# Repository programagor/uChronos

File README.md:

# uChronos
OSHW wristwatch which shows time in BCD

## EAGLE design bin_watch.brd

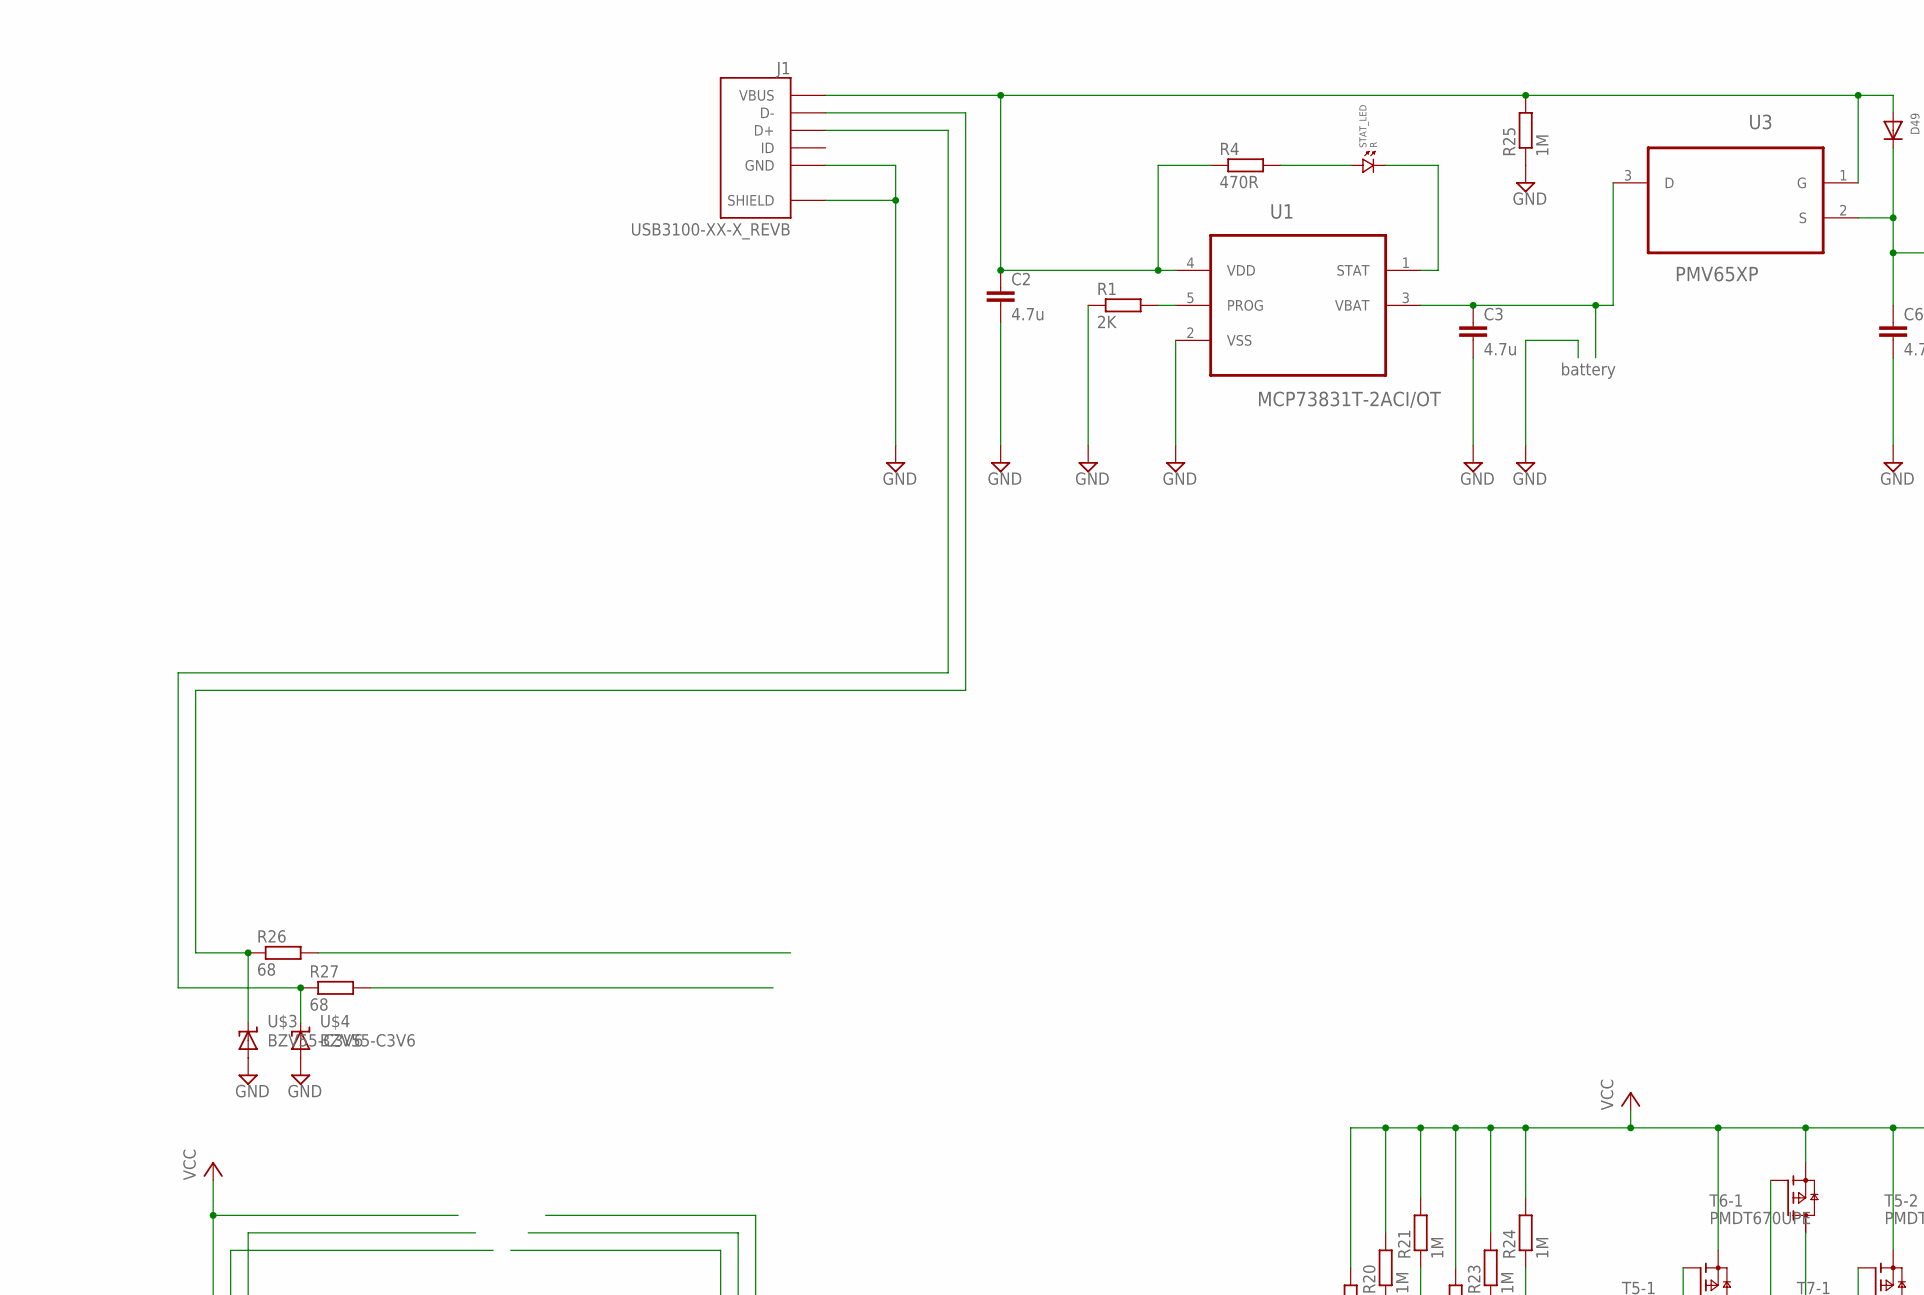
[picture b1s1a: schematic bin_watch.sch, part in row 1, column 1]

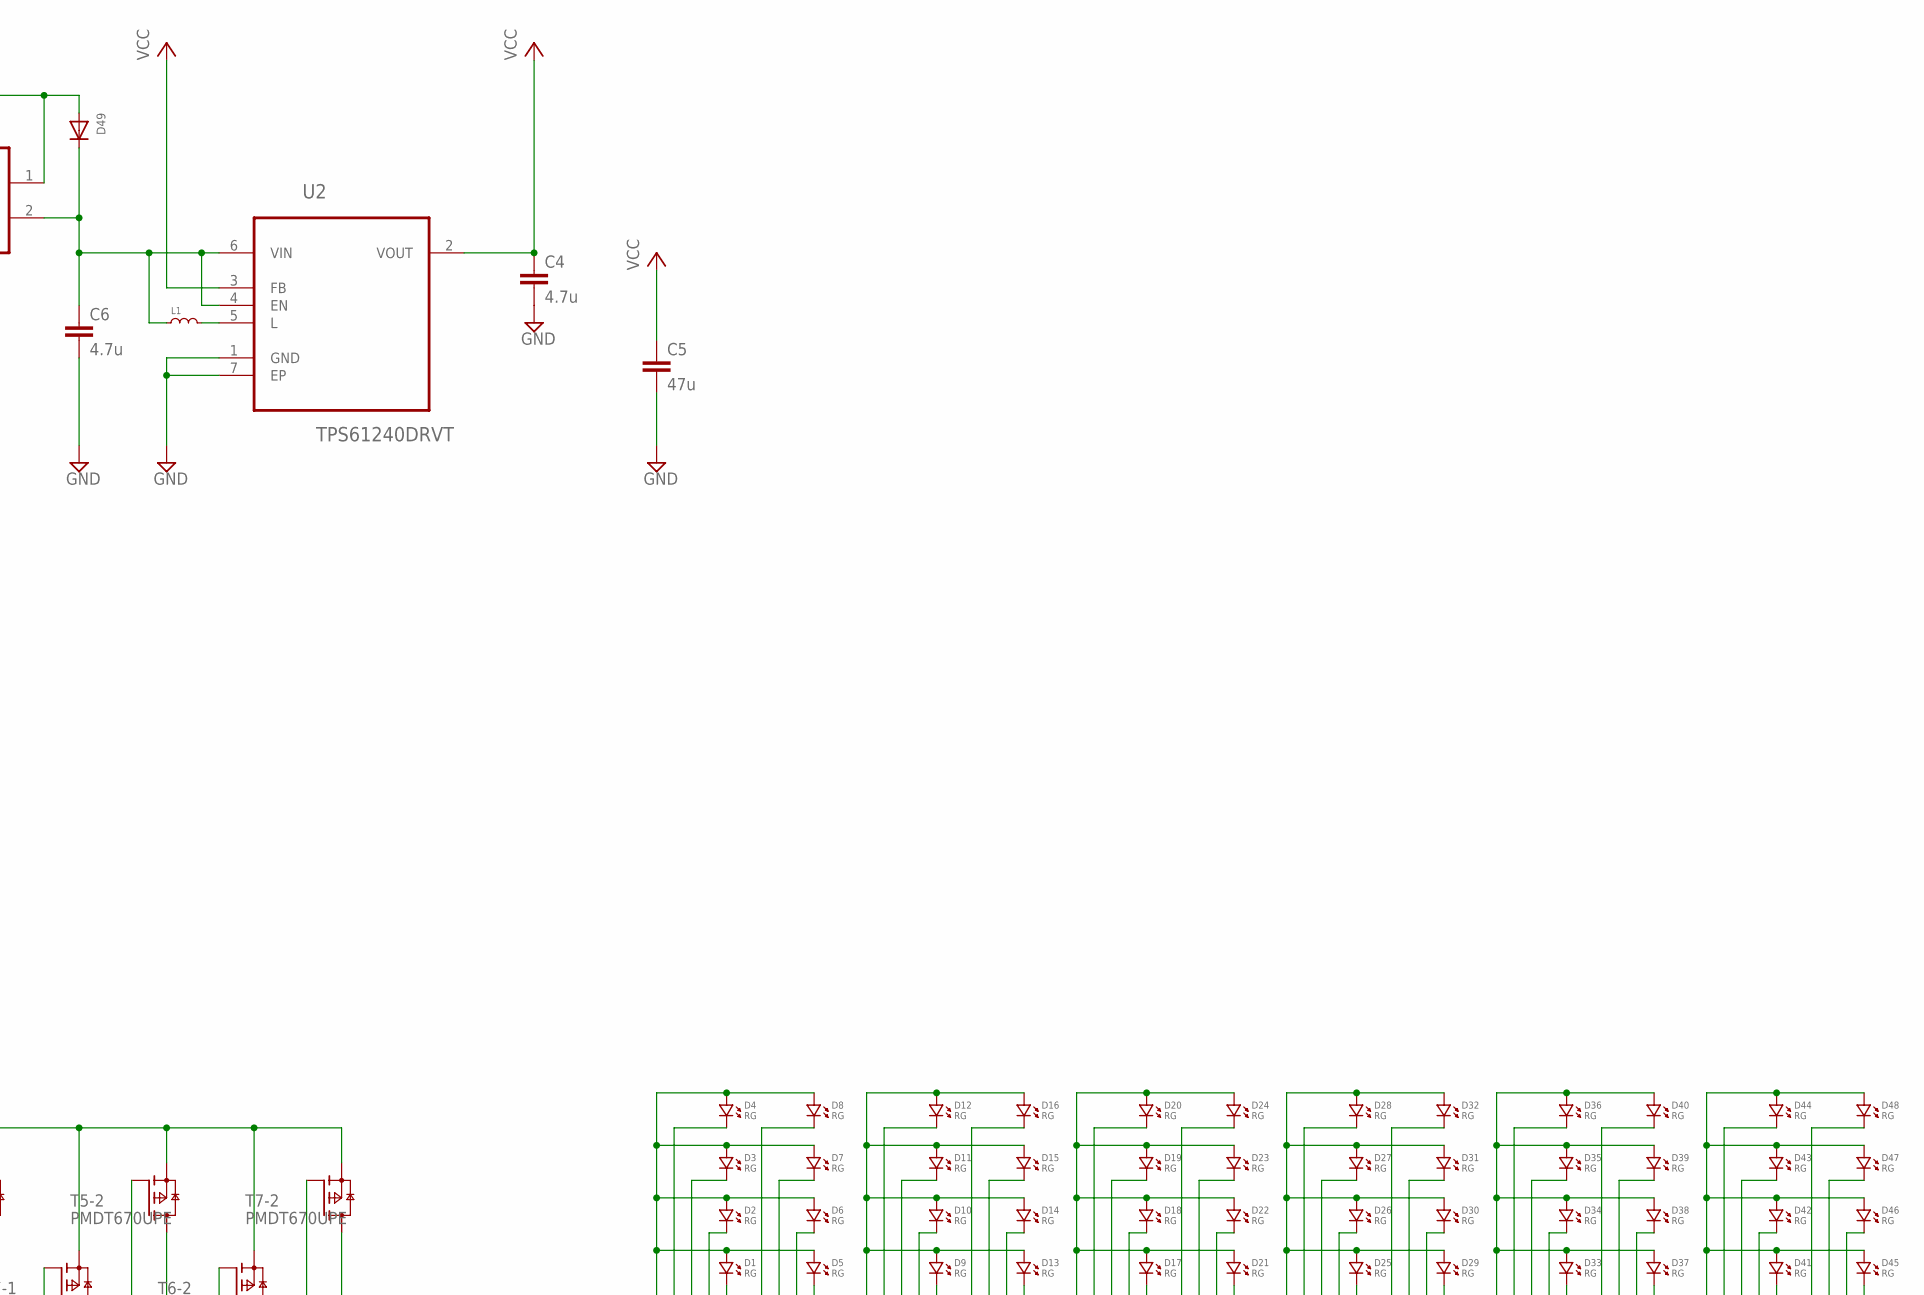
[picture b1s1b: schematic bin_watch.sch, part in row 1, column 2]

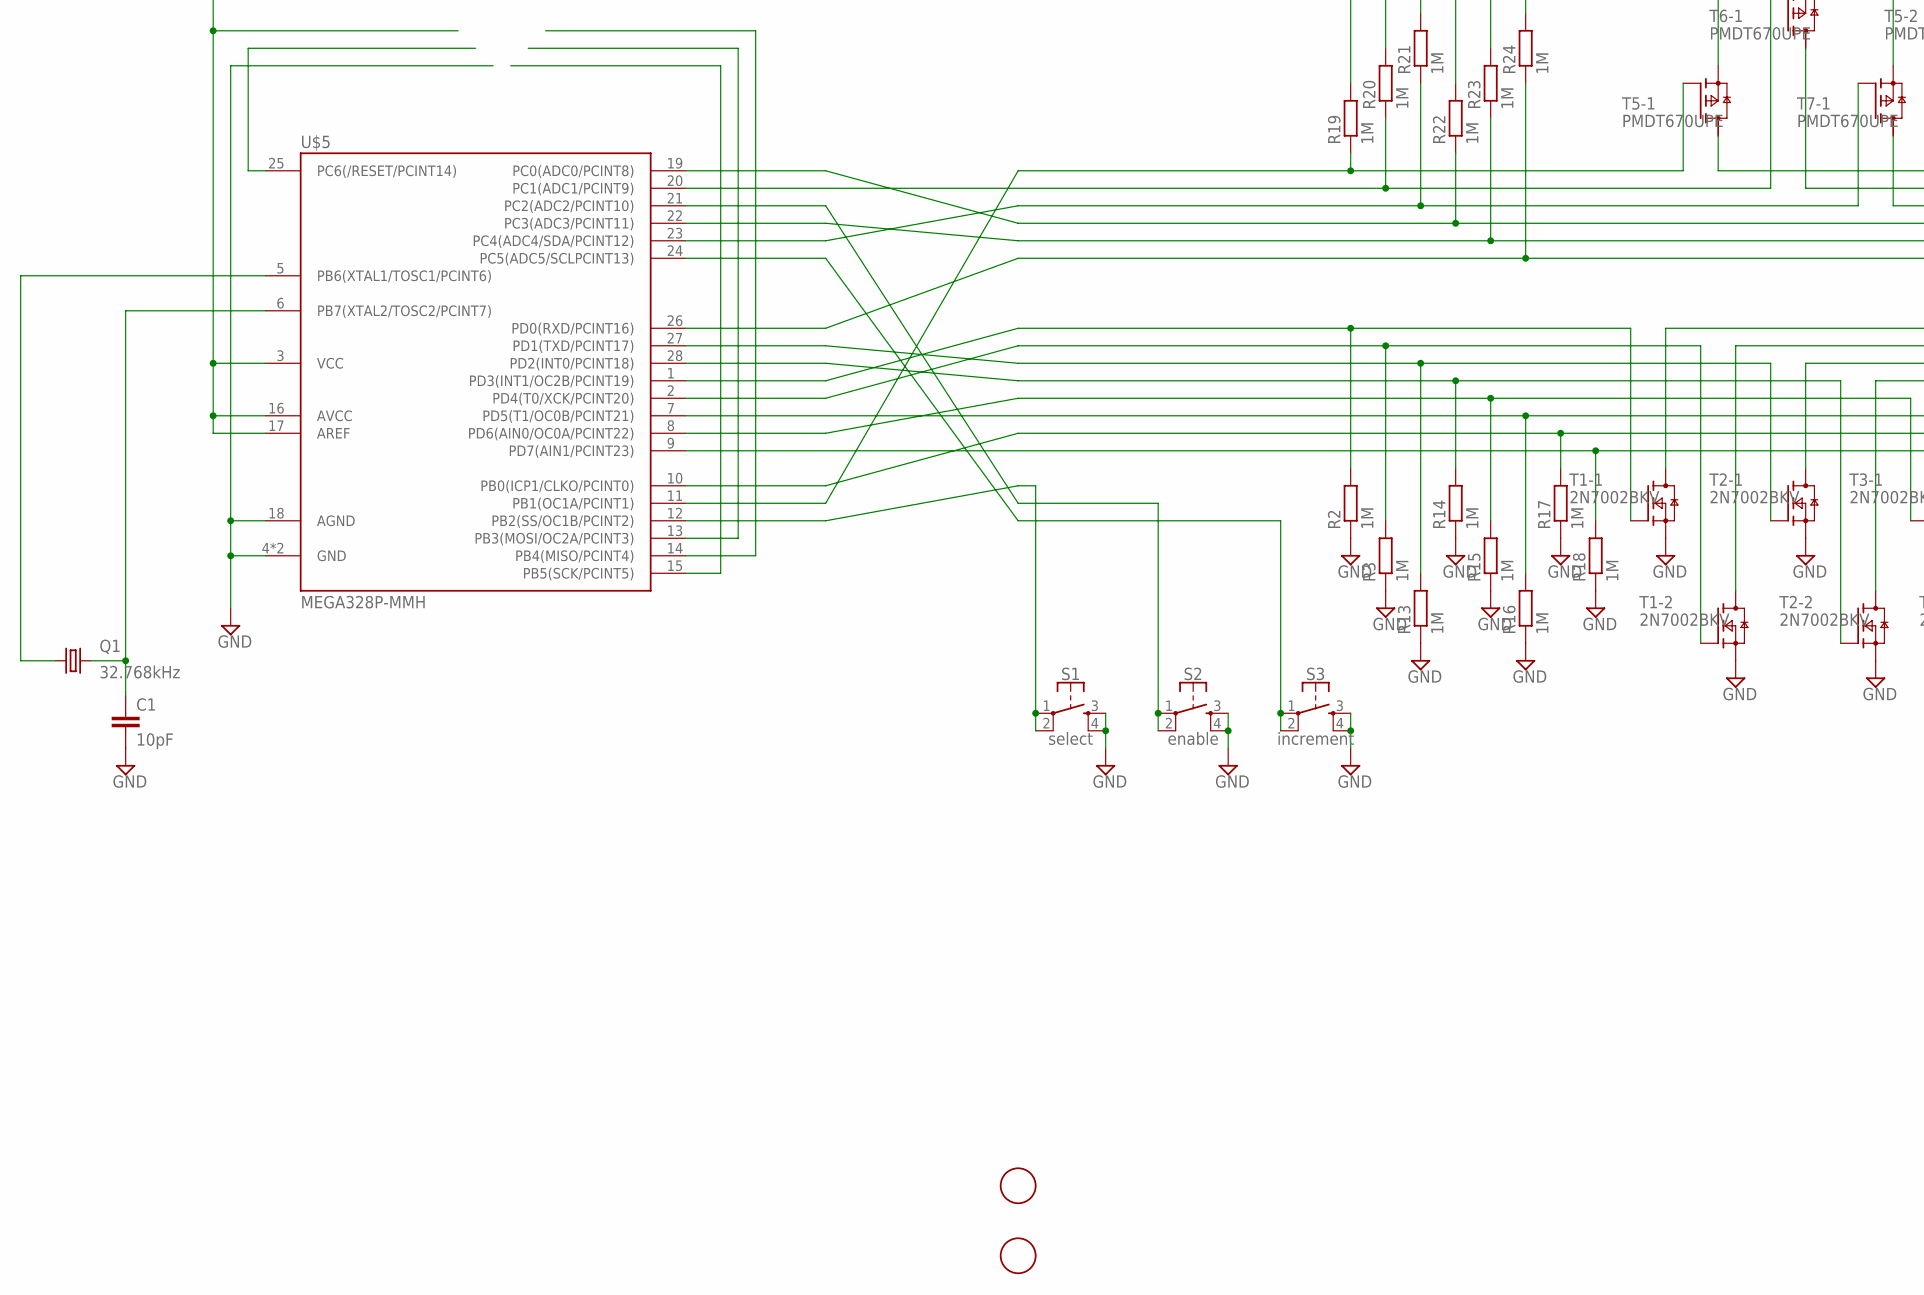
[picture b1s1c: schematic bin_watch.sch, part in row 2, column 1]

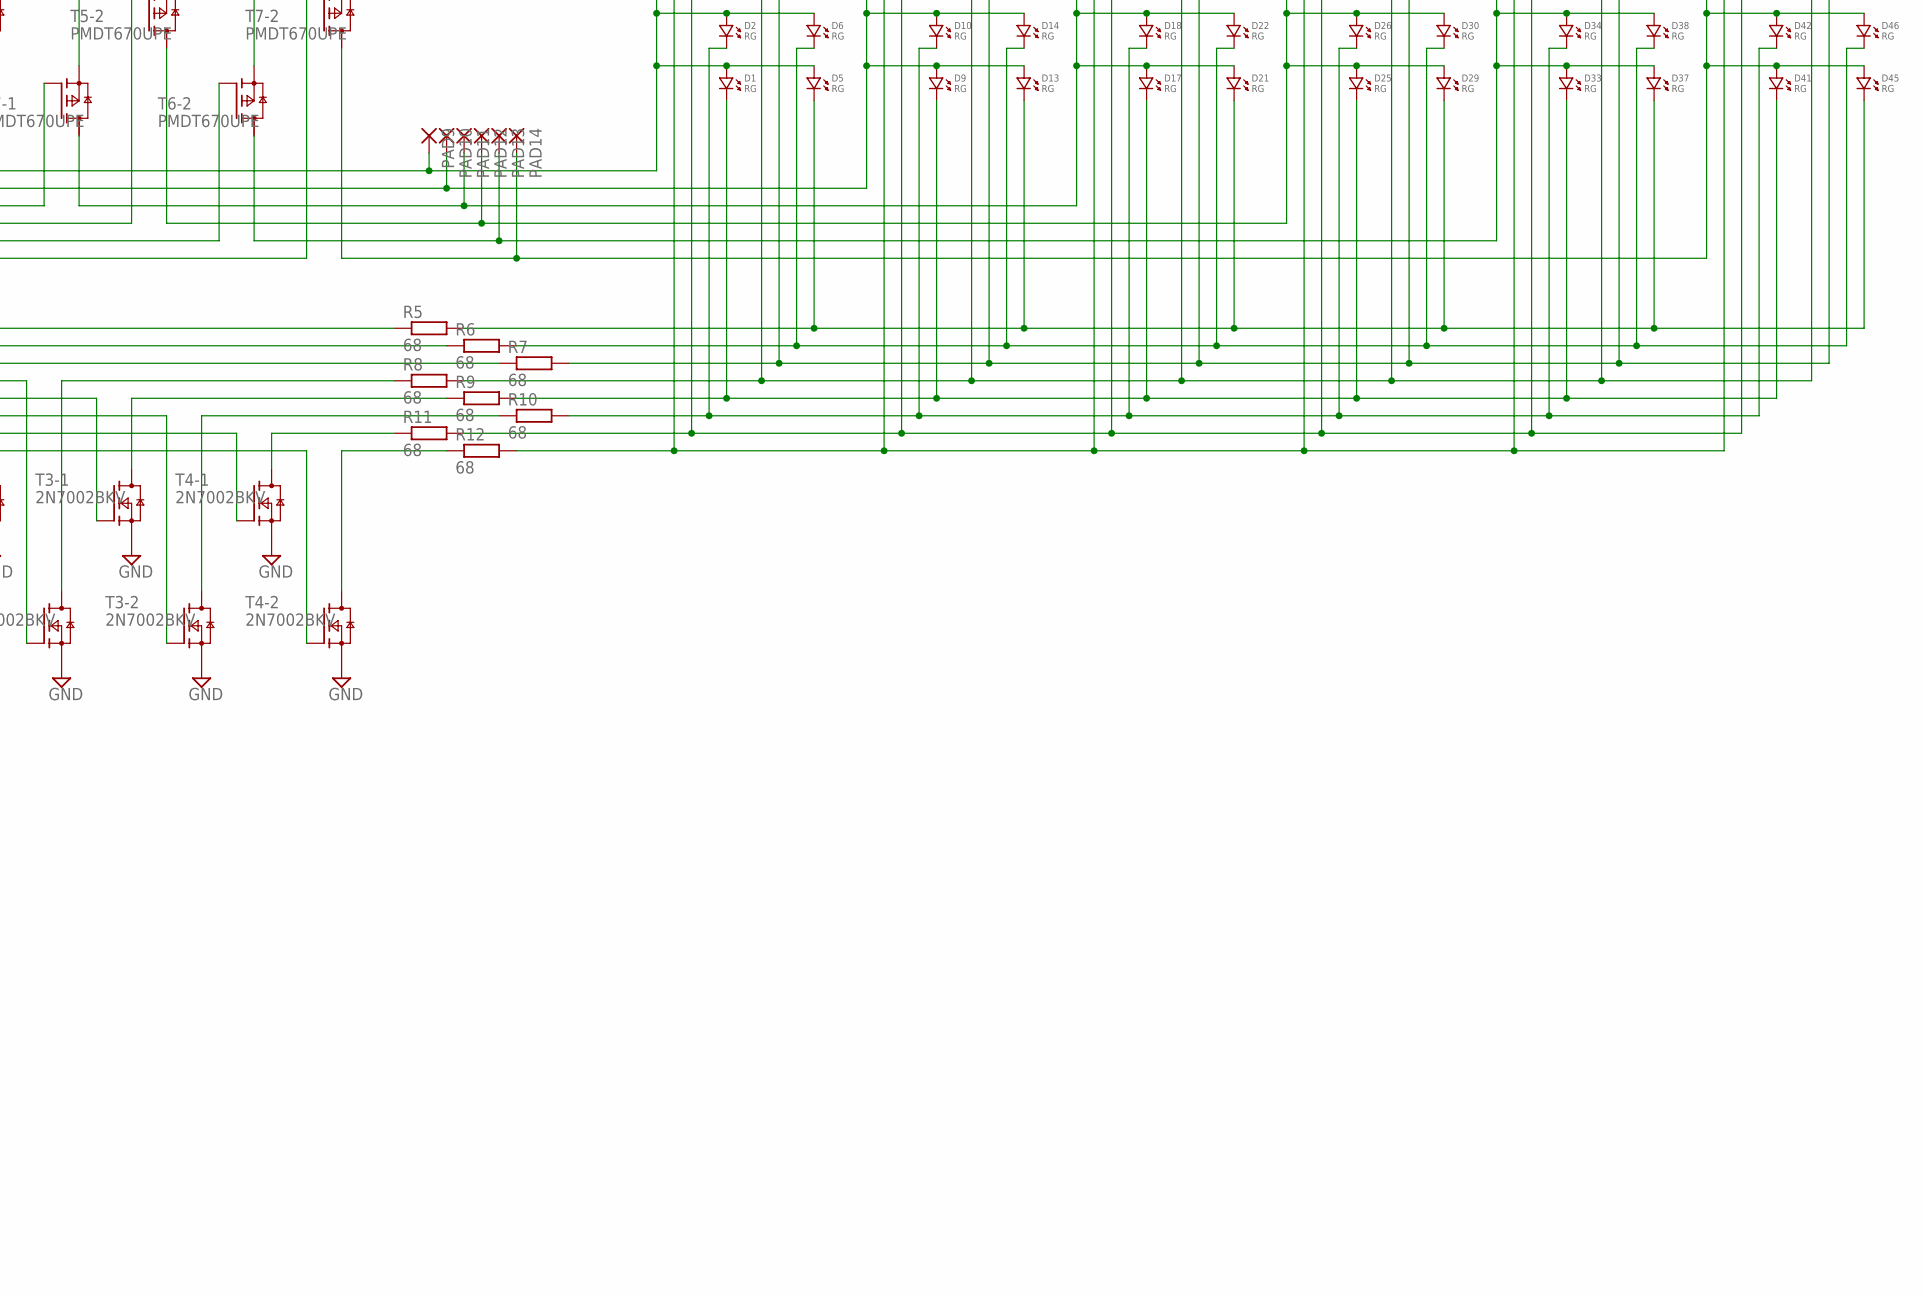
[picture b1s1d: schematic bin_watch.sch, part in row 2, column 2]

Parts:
C1: 10pF; C0603
C2, C3, C4, C6: 4.7u; C0603
C5: 47u; C0603
D1, D2, D3, D4, D5, D6, D7, D8, D9, D10, D11, D12, D13, D14, D15, D16, D17, D18, D19, D20, D21, D22, D23, D24, D25, D26, D27, D28, D29, D30, D31, D32, D33, D34, D35, D36, D37, D38, D39, D40, D41, D42, D43, D44, D45, D46, D47, D48: RG; 0603.LED
D49: DIODESOD-523; SOD-523
J1: USB3100-XX-X_REVB; GCT_USB3100-XX-X_REVB
L1: RF-INDUCTOR.0805; 0805
PAD9, PAD10, PAD11, PAD12, PAD13, PAD14: SMD2; SMD1,27-2,54
Q1: 32.768kHz; 3.2X1.5
R1: 2K; R0603
R2, R3, R13, R14, R15, R16, R17, R18, R19, R20, R21, R22, R23, R24, R25: 1M; R0603
R4: 470R; R0603
R5, R6, R7, R8, R9, R10, R11, R12, R26, R27: 68; R0603
S1: select; TACTILE_SWITCH_SMD_5.2MM
S2: enable; TACTILE_SWITCH_SMD_5.2MM
S3: increment; TACTILE_SWITCH_SMD_5.2MM
STAT_LED: R; 0603.LED
T1, T2, T3, T4: 2N7002BKV; SOT666
T5, T6, T7: PMDT670UPE; SOT666
U1: MCP73831T-2ACI/OT; SOT95P280X145-5N
U2: TPS61240DRVT; SON65P200X200X80-7N
U3: PMV65XP; SOT95P230X110-3N
U$1, U$2: FIDUCIAL; FIDUCIAL_1MM
U$3, U$4: BZV55-C3V6; SOD-80
U$5: MEGA328P-MMH; VQFN28

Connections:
BLOCK0: D1.P$1 (1), D2.P$1 (1), D3.P$1 (1), D4.P$1 (1), D5.P$1 (1), D6.P$1 (1), D7.P$1 (1), D8.P$1 (1), PAD9.1, T5.6 (D)
BLOCK1: D9.P$1 (1), D10.P$1 (1), D11.P$1 (1), D12.P$1 (1), D13.P$1 (1), D14.P$1 (1), D15.P$1 (1), D16.P$1 (1), PAD10.1, T6.6 (D)
BLOCK2: D17.P$1 (1), D18.P$1 (1), D19.P$1 (1), D20.P$1 (1), D21.P$1 (1), D22.P$1 (1), D23.P$1 (1), D24.P$1 (1), PAD11.1, T7.6 (D)
BLOCK3: D25.P$1 (1), D26.P$1 (1), D27.P$1 (1), D28.P$1 (1), D29.P$1 (1), D30.P$1 (1), D31.P$1 (1), D32.P$1 (1), PAD12.1, T5.3 (D)
BLOCK4: D33.P$1 (1), D34.P$1 (1), D35.P$1 (1), D36.P$1 (1), D37.P$1 (1), D38.P$1 (1), D39.P$1 (1), D40.P$1 (1), PAD13.1, T6.3 (D)
BLOCK5: D41.P$1 (1), D42.P$1 (1), D43.P$1 (1), D44.P$1 (1), D45.P$1 (1), D46.P$1 (1), D47.P$1 (1), D48.P$1 (1), PAD14.1, T7.3 (D)
BTN1: S1.1, S1.2, U$5.12 (PB2(SS/OC1B/PCINT2)); also elsewhere on the board
BTN2: S2.1, S2.2, U$5.21 (PC2(ADC2/PCINT10)); also elsewhere on the board
BTN3: S3.1, S3.2, U$5.24 (PC5(ADC5/SCLPCINT13)); also elsewhere on the board
D_N: J1.2 (D-), R26.1, U$3.C
D_P: J1.3 (D+), R27.1, U$4.C
GND: C1.2, C2.2, C3.2, C4.2, C5.2, C6.2, J1.5 (GND), J1.6 (SHIELD), J1.7 (SHIELD), J1.8 (SHIELD), J1.9 (SHIELD), R1.1, R2.1, R3.1, R13.1, R14.1, R15.1, R16.1, R17.1, R18.1, R25.1, S1.3, S1.4, S2.3, S2.4, S3.3, S3.4, T1.1 (S), T1.4 (S), T2.1 (S), T2.4 (S), T3.1 (S), T3.4 (S), T4.1 (S), T4.4 (S), U1.2 (VSS), U2.1 (GND), U2.7 (EP), U$3.A, U$4.A, U$5.4 (GND), U$5.18 (AGND); also elsewhere on the board
G_BLOCK0: R19.1, T5.2 (G), U$5.11 (PB1(OC1A/PCINT1)); also elsewhere on the board
G_BLOCK1: R20.1, T6.2 (G), U$5.20 (PC1(ADC1/PCINT9)); also elsewhere on the board
G_BLOCK2: R21.1, T7.2 (G), U$5.23 (PC4(ADC4/SDA/PCINT12)); also elsewhere on the board
G_BLOCK3: R22.1, T5.5 (G), U$5.19 (PC0(ADC0/PCINT8)); also elsewhere on the board
G_BLOCK4: R23.1, T6.5 (G), U$5.22 (PC3(ADC3/PCINT11)); also elsewhere on the board
G_BLOCK5: R24.1, T7.5 (G), U$5.26 (PD0(RXD/PCINT16)); also elsewhere on the board
G_LIGHT0: R2.2, T1.2 (G), U$5.1 (PD3(INT1/OC2B/PCINT19)); also elsewhere on the board
G_LIGHT1: R3.2, T1.5 (G), U$5.2 (PD4(T0/XCK/PCINT20)); also elsewhere on the board
G_LIGHT2: R13.2, T2.2 (G), U$5.27 (PD1(TXD/PCINT17)); also elsewhere on the board
G_LIGHT3: R14.2, T2.5 (G), U$5.28 (PD2(INT0/PCINT18)); also elsewhere on the board
G_LIGHT4: R15.2, T3.2 (G), U$5.8 (PD6(AIN0/OC0A/PCINT22)); also elsewhere on the board
G_LIGHT5: R16.2, T3.5 (G), U$5.7 (PD5(T1/OC0B/PCINT21)); also elsewhere on the board
G_LIGHT6: R17.2, T4.2 (G), U$5.10 (PB0(ICP1/CLKO/PCINT0)); also elsewhere on the board
G_LIGHT7: R18.2, T4.5 (G), U$5.9 (PD7(AIN1/PCINT23)); also elsewhere on the board
L: L1.2, U2.5 (L)
LIGHT0: D5.P$2 (2), D13.P$2 (2), D21.P$2 (2), D29.P$2 (2), D37.P$2 (2), D45.P$2 (2), R5.2
LIGHT1: D6.P$2 (2), D14.P$2 (2), D22.P$2 (2), D30.P$2 (2), D38.P$2 (2), D46.P$2 (2), R6.2
LIGHT2: D7.P$2 (2), D15.P$2 (2), D23.P$2 (2), D31.P$2 (2), D39.P$2 (2), D47.P$2 (2), R7.2
LIGHT3: D8.P$2 (2), D16.P$2 (2), D24.P$2 (2), D32.P$2 (2), D40.P$2 (2), D48.P$2 (2), R8.2
LIGHT4: D1.P$2 (2), D9.P$2 (2), D17.P$2 (2), D25.P$2 (2), D33.P$2 (2), D41.P$2 (2), R9.2
LIGHT5: D2.P$2 (2), D10.P$2 (2), D18.P$2 (2), D26.P$2 (2), D34.P$2 (2), D42.P$2 (2), R10.2
LIGHT6: D3.P$2 (2), D11.P$2 (2), D19.P$2 (2), D27.P$2 (2), D35.P$2 (2), D43.P$2 (2), R11.2
LIGHT7: D4.P$2 (2), D12.P$2 (2), D20.P$2 (2), D28.P$2 (2), D36.P$2 (2), D44.P$2 (2), R12.2
PROG: R1.2, U1.5 (PROG)
R_LIGHT0: R5.1, T1.6 (D)
R_LIGHT1: R6.1, T1.3 (D)
R_LIGHT2: R7.1, T2.6 (D)
R_LIGHT3: R8.1, T2.3 (D)
R_LIGHT4: R9.1, T3.6 (D)
R_LIGHT5: R10.1, T3.3 (D)
R_LIGHT6: R11.1, T4.6 (D)
R_LIGHT7: R12.1, T4.3 (D)
STAT: STAT_LED.P$2 (2), U1.1 (STAT)
STAT_R: R4.2, STAT_LED.P$1 (1)
VBATT: C3.1, U1.3 (VBAT), U3.3 (D); also elsewhere on the board
VBUS: C2.1, D49.A, J1.1 (VBUS), R4.1, R25.2, U1.4 (VDD), U3.1 (G)
VCC: C4.1, C5.1, R19.2, R20.2, R21.2, R22.2, R23.2, R24.2, T5.1 (S), T5.4 (S), T6.1 (S), T6.4 (S), T7.1 (S), T7.4 (S), U2.2 (VOUT), U2.3 (FB), U$5.3 (VCC), U$5.16 (AVCC), U$5.17 (AREF); also elsewhere on the board
VIN: C6.1, D49.K (C), L1.1, U2.4 (EN), U2.6 (VIN), U3.2 (S)
XTAL_N: C1.1, Q1.2, U$5.6 (PB7(XTAL2/TOSC2/PCINT7)); also elsewhere on the board
XTAL_P: Q1.1, U$5.5 (PB6(XTAL1/TOSC1/PCINT6)); also elsewhere on the board

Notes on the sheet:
battery

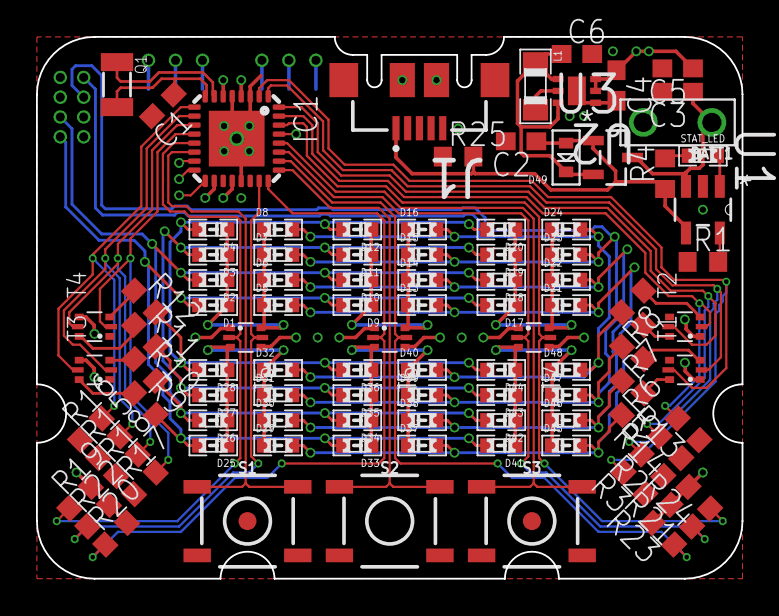
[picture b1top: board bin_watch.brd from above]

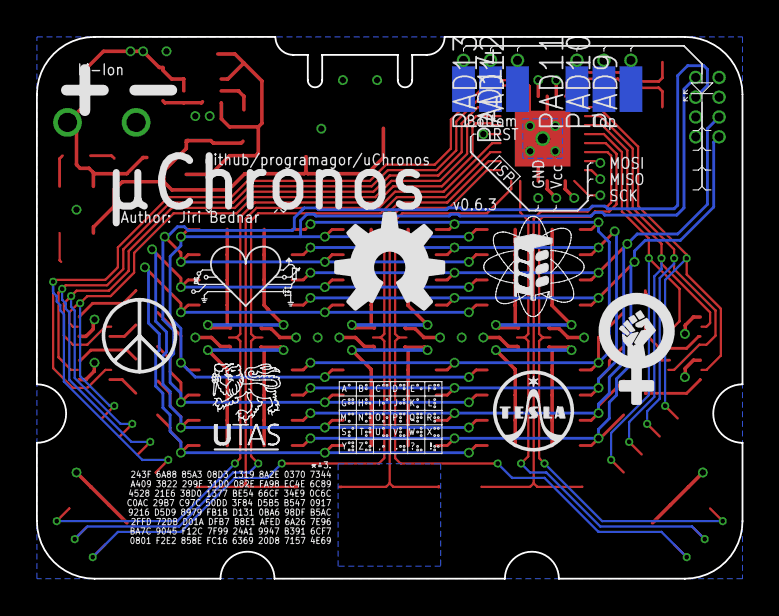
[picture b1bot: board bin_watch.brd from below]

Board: 4 copper layers, 39.2 x 30.1 mm, 107 parts (6 on the bottom side), 50 nets.

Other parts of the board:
BATT1: 56455 201 012; 1X02_BIG
IC1: MEGA48/88/168-MU; MLF32

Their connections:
BTN1: IC1.14; also elsewhere on the board
BTN2: IC1.25; also elsewhere on the board
BTN3: IC1.28; also elsewhere on the board
GND: BATT1.P$2, IC1.3, IC1.5, IC1.21; also elsewhere on the board
G_BLOCK0: IC1.13; also elsewhere on the board
G_BLOCK1: IC1.24; also elsewhere on the board
G_BLOCK2: IC1.27; also elsewhere on the board
G_BLOCK3: IC1.23; also elsewhere on the board
G_BLOCK4: IC1.26; also elsewhere on the board
G_BLOCK5: IC1.30; also elsewhere on the board
G_LIGHT0: IC1.1; also elsewhere on the board
G_LIGHT1: IC1.2; also elsewhere on the board
G_LIGHT2: IC1.31; also elsewhere on the board
G_LIGHT3: IC1.32; also elsewhere on the board
G_LIGHT4: IC1.10; also elsewhere on the board
G_LIGHT5: IC1.9; also elsewhere on the board
G_LIGHT6: IC1.12; also elsewhere on the board
G_LIGHT7: IC1.11; also elsewhere on the board
VBATT: BATT1.P$1; also elsewhere on the board
VCC: IC1.4, IC1.6, IC1.18, IC1.20; also elsewhere on the board
XTAL_N: IC1.8; also elsewhere on the board
XTAL_P: IC1.7; also elsewhere on the board

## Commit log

2017-08-15 Initial commit
    First version of the schematics and the board
2017-08-15 Route cleanup
    I ditched the auto-routed traces, and hand-routed everything. This should be much easier to work with.
2017-08-15 Switched to Li-ion
    The button cell i not up to the task, so we need a Li-ion battery.
2017-08-15 Switched to switching supply
    The linear regulator is not very efficient, swapping it for a buck converter.
2017-08-15 Added dummy firmware
    Written for my previous version, not compatible with this hardware.
    TODO: Rewrite for this configuration.
2017-08-15 Added I limiting resistors
    Relying on the FETs to limit the current to diodes is not very safe, so added resistors to do that. It's a tight squeeze, but it fits.
2017-08-15 Added board preview
    Image showing all relevant layers
2017-08-15 Started firmware from scratch
    Initial Atmel Studio files
2017-08-15 Program skeleton
    IVT inserted, no functionality implemented
2017-08-15 Added pendulum and incrementor files
    Pendulum contains code that is called every 1 second. Incrementors add numbers to displayed digits.
2017-08-16 Added notes
    To keep track of the design decisions that were made
2017-08-16 Added 3D views of the board
2017-08-16 Added BOM
    Bill of materials, format:
    Part, manufacturer code, element14 order code, amount
2017-08-16 Added potentiometer
    This is to enable small adjustments to the system voltage around 3.5 V
2017-08-16 Updated BOM
    Now all components are 0603
2017-08-16 Little tweaks
    Ipdated component names, positions, and version label.
2017-08-17 Added more base code
    Port initialisation after reset, and RTC timer configuration
2017-08-21 Small tweaks to traces
2017-08-23 Small tweaks
    Fixed non-n45° traces.
    TODO: mirror the QR code
2017-08-23 v0.5 - Incremented displayed number
    The PCB now shows v0.5 as the version.
2017-08-23 Mirrored the QR code
    Now the QR code on the bottom side has the right orientation.
2017-08-26 More tweaking
    Fixed some angles and spacing, improved groundfill slightly. Fixed the QR code (inverted, mirrored).
2017-08-27 Added Gerber files, small tweaks to the board
    Gerbers optimised for PCBway, but probably acceptable by most other fabs.
    The board now has little holes around the big mounting holes, ostensibly to increase the durability/redundancy of the inner plating, but the real reason is that it looks cool.
2017-09-05 Added fiducial marks
    Some minor adjustments to the traces, and added fiducial marks for the board and for the chip.
2017-09-17 Fixed silkscreen width issue
    MetaLab logo now renders correctly at 500 DPI
2017-09-17 Changed power supply to 5V
    Replaced the Buck converter with a Boost converter. Saved some space.
2017-09-17 Removed mounting holes
    Saved a lot more space
2017-09-17 Added charger isolation
    When the battery is being charged, the Boost converter is powered directly from USB rather than through the charger.
2017-09-17 4-layer design
    Now using ground and power plane
2017-09-18 QFN
    ATmega328 now a QFN-32
    TODO: place components, route
2017-09-18 Replaced AVR ISP with smaller pads
2017-09-19 IOs rewired
    Changed the IO wiring to reduce the number of vias.
    TODO: Power supply routing
2017-09-19 Board shrunk
    Sized down version
    TODO: Power supply routing
2017-09-19 Fully routed
2017-09-19 Added pull resistors to N-gates
    Thois way, when the gates are not driven, they'll default to open-circuit.
2017-09-19 Revert "Added pull resistors to N-gates"
    This reverts commit 9868d69179800805ca64c73f808847093c2a5451.
2017-09-19 Added pull resistors to N-channels
    This way, when the gates are not driven, they default to OFF
2017-09-19 Pull resistors for N-channels routed
2017-09-20 Added solder pads for blocks
2017-09-23 Started routing wirepads to drivers
    So that the board can be used as a driver for external loads
2017-09-28 Mass commit
    This is a mess...
    Added a new firmware attempt, this time in C language.
    Several changes to the board
    A a pull resistor for the gate of the power transistor
    Stuff I forgot...
2017-09-29 Added disp_utils
    Now it can fill display, clear display, and show time (blocks maskable)
2017-09-29 Added support for buttons
    And a lot of other things
2017-10-02 Introduced the state machine
    Now a lot of functions are available, and a mechanism for general state transitions with button presses (down and up event).
    Function pointers are cool!
2017-10-03 Added simple menu structure
    Now the state machine is used to determine user's position in the view/menu. Graph of this state machine is provided in figure 82.6 of The 8th Book of Things.
2017-10-03 Simplified state transitions
    Now no need to specify function pointers, state transition is the assumed action (no transition if 0xFF is the target state)
2017-10-04 Renamed btn_{down,up}_arg to btn_down_next
    for some reason, this is perhaps clearer (..._next_state would be really clear here)
2017-10-08 More states
    I need to rethink this...
2017-10-14 Everything fully routed
2017-10-15 Updated board preview
2017-10-16 Added mounting notches
2017-10-16 Gerbers updated
2017-10-16 Fixed bottom silkscreen in Gerbers
2017-10-16 Fixed errors in bottom silkscreen
    Now it's presentable
2017-10-16 Added Braille Alphabet to bottom silkscreen
2017-10-16 Added TESLA logo
2017-10-19 Small adjustments
    Silkscreen, spacing, and other little things
2017-10-22 Added gerber with teardrops on vias
2017-10-24 Routing optimisation
    Some splits removed frominternal groundplane
2017-10-24 Added groundpad
    The library file was missing soldermask for the groundpad, so one was added manually.
2017-10-25 Fixed broken build of FW
    Bad naming convention in the state machine
2017-10-26 Added UTAS logo to bottom silkscreen (WIP)
    Lion head needs to be finished
2017-10-26 More work on the lion (WIP)
2017-10-26 Even more work on the lion (WIP)
    Now only need to do the mane
2017-10-26 UTAS logo finished
2017-10-28 Small silkscreen changes
2017-10-30 More stuff added to silkscreen
    Feminism and Hippie logo
2017-10-30 Gerber files updated to current board version
2017-11-01 Fixed bad paste layer
    Added 1mil-2.5mil gap between pad edge and paste
2017-11-06 Added board images
    Rendered by OSHpark
2017-11-09 Straightend some tiny kinks on a fw lines
2017-11-10 Removed QFN32, placed QFN28
2017-11-10 New chip wired to IO
2017-11-11 Routing UC to IO
    WIP
2017-11-11 More routing
    WIP
2017-11-11 Routed IO
    TODO: ISP
2017-11-12 Vias on ISP lines
2017-11-12 Gap between row solderpads reduced
2017-11-13 Assortment of tiny tweaks
    Made some wires closer together, and other stuff I forgot
2017-11-14 Fixed extraneous tStop rectangle
    and some other small changes
2017-11-14 More tweaks
    Moved some wires around
2017-11-16 Made the external connctor smaller
2017-11-17 Crystal moved out of the way
2017-11-19 Moved connector up
2017-11-20 Remove old versions of firmware
2017-11-20 Separated display and time functionality
2017-11-20 Display refresher encapsulated
2017-11-21 Synchronous operation calibrated
2017-11-25 Moved crystal
    TODO: Pick existing uC for ISP
2017-11-27 Removed FW build junk files
2017-11-28 Fixed undocumented clearance violations
2017-12-01 Replaced 328p with 4x4mm VQFN
2017-12-01 Lot of other changes
2017-12-01 Fixed the state machine's init_text function
2017-12-01 Finished time config menu
2017-12-03 Basic snake walk implemented
2017-12-03 Fixed some modulo errors (edge cases)
2017-12-03 fixed rollover bug
2017-12-03 Compactified mapping between sequence number and disp_mem
2017-12-16 Added comment to cryptic line
2017-12-17 IO wired, USB disconnected
2018-02-14 Changed fonts to Vector

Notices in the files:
parts and their libraries:
SparkFun-Switches: Licensing: Creative Commons ShareAlike 4.0 International - https://creativecommons.org/licenses/by-sa/4.0
crystal-geyer_V1_0: Copyright: Geyer-Electronic
